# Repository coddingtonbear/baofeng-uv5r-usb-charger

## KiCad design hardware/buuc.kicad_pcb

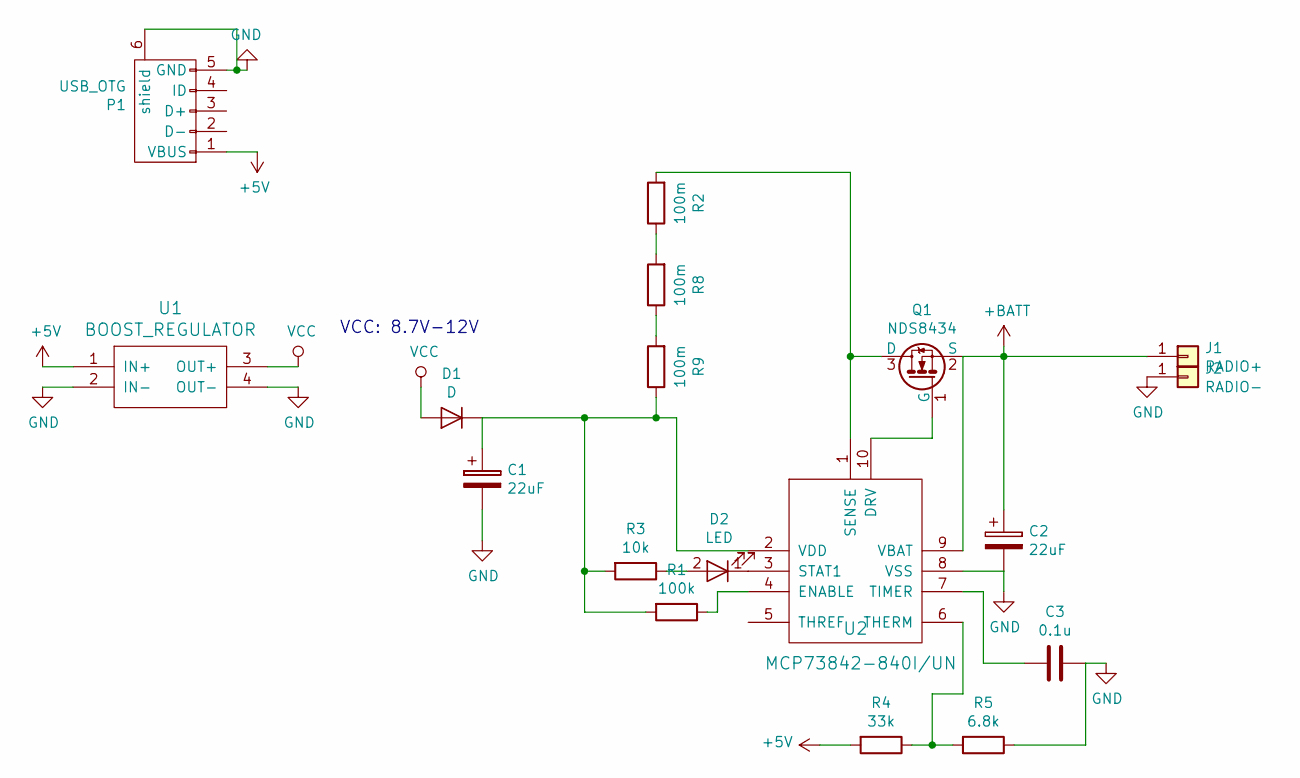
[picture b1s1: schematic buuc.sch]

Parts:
C1, C2: 22uF; C_1206_HandSoldering
C3: 0.1u; 0805_Milling
D1: D; DO-214AA-SMB
D2: LED; 0805_Milling
J1: RADIO+; TAB
J2: RADIO-; TAB
P1: USB_OTG; UJ2-MIBH-4-SMT
Q1: NDS8434
R1: 100k; 0805_Milling
R2, R8, R9: 100m; 0805_Milling
R3: 10k; 0805_Milling
R4: 33k; 0805_Milling
R5: 6.8k; 0805_Milling
U1: BOOST_REGULATOR
U2: MCP73842-840I/UN; MSOP-10

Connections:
+5V: P1.1 (VBUS), R4.2, U1.1 (IN+)
+BATT: C2.1, J1.1, Q1.2 (S), U2.9 (VBAT)
GND: C1.2, C2.2, C3.1, J2.1, P1.5 (GND), P1.6 (shield), R5.1, U1.2 (IN-), U1.4 (OUT-), U2.8 (VSS)
unnamed: C1.1, D1.1 (K), R1.2, R3.2, R9.1, U2.2 (VDD)
unnamed: C3.2, U2.7 (TIMER)
unnamed: D2.1 (K), U2.3 (STAT1)
unnamed: D2.2 (A), R3.1
unnamed: Q1.1 (G), U2.10 (DRV)
unnamed: Q1.3 (D), R2.2, U2.1 (SENSE)
unnamed: R1.1, U2.4 (ENABLE)
unnamed: R2.1, R8.2
unnamed: R4.1, R5.2, U2.6 (THERM)
unnamed: R8.1, R9.2
VCC: D1.2 (A), U1.3 (OUT+)

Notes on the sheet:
VCC: 8.7V-12V

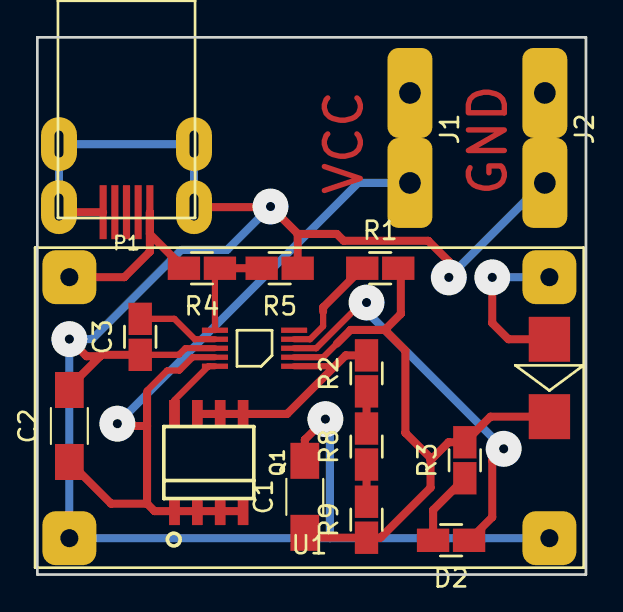
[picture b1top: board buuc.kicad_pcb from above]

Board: 2 copper layers, 30.5 x 29.8 mm, 18 parts (0 on the bottom side), 14 nets.

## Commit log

2017-09-06 Adding new hardware designs.
2017-09-06 Whoops; using the wrong footprint and chip diagram.
2017-09-06 Minor changes to ground plane clearances to improve milling.
2017-09-06 Committing changes from yesterday.
2017-09-10 Minor pcb changes.
2017-09-10 Minor updates; fixing size of boost regulator board.
2017-09-14 Updating schematics.
2017-09-14 Adding MIC2005 current limiting IC; I haven't even soldered everything together, but it's pretty clear this will be necessary.
2017-09-15 Swapping resistor footprint for one that's a bit easier to solder onto a milled board; minor move of the USB connector.
2017-09-15 Slightly more space is necessary.
2017-09-15 Even more space...
2017-09-17 Apparently: active low. FFS.
2017-09-19 Adding extra pads allowing me to fine-tune the consumed current; adding unpopulated bypass resistor around the MIC2005.
2017-09-19 fixup! Adding extra pads allowing me to fine-tune the consumed current; adding unpopulated bypass resistor around the MIC2005.
2017-09-19 Updating to use a grid of current sense resistors for configurability.
2017-09-23 Switch to through-hole USB adapter; the SMD component is a little too jiggly, and I don't have better ones on-hand at the moment.
2017-10-02 If I'm going to do this another time, I might as well make it count.
2017-10-15 Slightly more compact.
2017-10-15 Updating to use slightly-wider tracks.
